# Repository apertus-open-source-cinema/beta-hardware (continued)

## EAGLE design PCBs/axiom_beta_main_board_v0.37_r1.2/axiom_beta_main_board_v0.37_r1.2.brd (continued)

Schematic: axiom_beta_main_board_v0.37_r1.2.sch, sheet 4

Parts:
C1, C1', C3, C3', C5, C5', C7, C7': C0805-A; 0805-A
C2, C2', C4, C4', C6, C6', C8, C8': C0603-A; 0603-A
PAD1, PAD2, PAD3, PAD4, PAD5, PAD6, PAD7, PAD8, PAD9, PAD10, PAD11, PAD12, PAD13, PAD14, PAD15, PAD16: PINPAD1.27MM; 1.2/0.6
PB-NW: DF12(XX)-20DP-0.5V
PB-SE: DF12(XX)-20DP-0.5V
PCIE-NORTH: PCIE-36-AXIOM-NOPEG; PCIE-36-NOPEG
PCIE-SOUTH: PCIE-36-AXIOM-NOPEG; PCIE-36-NOPEG
PWR-NE: PINHD-2X02_2.54; 2X02
PWR-NW: PINHD-2X02_2.54; 2X02
PWR-SE: PINHD-2X02_2.54; 2X02
PWR-SW: PINHD-2X02_2.54; 2X02
R1, R2, R3, R4, R5, R6: 4k7; 0402-B
U1: PCA9540BDP; SOP65P490X300-8N

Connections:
A_!RST: PB-NW.2; also elsewhere on the board
A_SCL: PB-NW.1; also elsewhere on the board
A_SDA: PB-NW.3; also elsewhere on the board
BANK13_00_N: PCIE-NORTH.B17 (LVDS_5B); also elsewhere on the board
BANK13_00_P: PCIE-NORTH.B16 (LVDS_5A); also elsewhere on the board
BANK13_02_N: PCIE-NORTH.A16 (LVDS_4A); also elsewhere on the board
BANK13_02_P: PCIE-NORTH.A17 (LVDS_4B); also elsewhere on the board
BANK13_03_N: PCIE-NORTH.A14 (LVDS_3B); also elsewhere on the board
BANK13_03_P: PCIE-NORTH.A13 (LVDS_3A); also elsewhere on the board
BANK13_04_N: PCIE-SOUTH.A6 (LVDS_1B); also elsewhere on the board
BANK13_04_P: PCIE-SOUTH.A5 (LVDS_1A); also elsewhere on the board
BANK13_05_N: PCIE-SOUTH.A3 (LVDS_0B); also elsewhere on the board
BANK13_05_P: PCIE-SOUTH.A2 (LVDS_0A); also elsewhere on the board
BANK13_06_N: PCIE-SOUTH.A8 (LVDS_2A); also elsewhere on the board
BANK13_06_P: PCIE-SOUTH.A9 (LVDS_2B); also elsewhere on the board
B_!RST: PB-SE.2; also elsewhere on the board
B_SCL: PB-SE.1; also elsewhere on the board
B_SDA: PB-SE.3; also elsewhere on the board
CSO_NE_V: C3.1, C3'.1, C4.1, C4'.1, PAD2.1; also elsewhere on the board
CSO_NW_V: C1.1, C1'.1, C2.1, C2'.1, PAD15.1, PWR-NW.1
CSO_SE_V: C7.1, C7'.1, C8.1, C8'.1, PAD7.1, PWR-SE.1
CSO_SW_V: C5.1, C5'.1, C6.1, C6'.1, PAD10.1; also elsewhere on the board
C_CK_E: PAD5.1; also elsewhere on the board
C_CK_W: PAD13.1; also elsewhere on the board
C_EN_E: PAD3.1; also elsewhere on the board
C_EN_W: PAD11.1; also elsewhere on the board
C_SI_E: PAD4.1; also elsewhere on the board
C_SI_W: PAD12.1; also elsewhere on the board
C_SO_E: PAD6.1; also elsewhere on the board
C_SO_W: PAD14.1; also elsewhere on the board
E_I2C_V: PWR-NE.1; also elsewhere on the board
E_SPI_V: PWR-NE.3; also elsewhere on the board
E_VE_CV: PB-SE.19; also elsewhere on the board
E_VE_OV: PB-SE.10; also elsewhere on the board
E_VE_UV: PB-SE.12; also elsewhere on the board
GND: C1.2, C1'.2, C2.2, C2'.2, C3.2, C3'.2, C4.2, C4'.2, C5.2, C5'.2, C6.2, C6'.2, C7.2, C7'.2, C8.2, C8'.2, PAD1.1, PAD8.1, PAD9.1, PAD16.1, PB-NW.5, PB-SE.5, PCIE-NORTH.A1 (GND), PCIE-NORTH.A4 (GND), PCIE-NORTH.A7 (GND), PCIE-NORTH.A10 (GND), PCIE-NORTH.A12 (GND), PCIE-NORTH.A15 (GND), PCIE-NORTH.A18 (GND), PCIE-NORTH.B15 (GND), PCIE-NORTH.B18 (GND), PCIE-SOUTH.A1 (GND), PCIE-SOUTH.A4 (GND), PCIE-SOUTH.A7 (GND), PCIE-SOUTH.A10 (GND), PCIE-SOUTH.A12 (GND), PCIE-SOUTH.A15 (GND), PCIE-SOUTH.A18 (GND), PCIE-SOUTH.B15 (GND), PCIE-SOUTH.B18 (GND), U1.6 (VSS); also elsewhere on the board
JTAG_V: PWR-SW.3; also elsewhere on the board
JX1_19_N: PCIE-NORTH.A3 (LVDS_0B); also elsewhere on the board
JX1_19_P: PCIE-NORTH.A2 (LVDS_0A); also elsewhere on the board
JX1_21_N: PCIE-NORTH.A6 (LVDS_1B); also elsewhere on the board
JX1_21_P: PCIE-NORTH.A5 (LVDS_1A); also elsewhere on the board
JX1_23_N: PCIE-NORTH.A9 (LVDS_2B); also elsewhere on the board
JX1_23_P: PCIE-NORTH.A8 (LVDS_2A); also elsewhere on the board
JX2_18_N: PCIE-SOUTH.B17 (LVDS_5B); also elsewhere on the board
JX2_18_P: PCIE-SOUTH.B16 (LVDS_5A); also elsewhere on the board
JX2_20_N: PCIE-SOUTH.A17 (LVDS_4B); also elsewhere on the board
JX2_20_P: PCIE-SOUTH.A16 (LVDS_4A); also elsewhere on the board
JX2_22_N: PCIE-SOUTH.A13 (LVDS_3A); also elsewhere on the board
JX2_22_P: PCIE-SOUTH.A14 (LVDS_3B); also elsewhere on the board
N_CHK_V: PB-NW.14; also elsewhere on the board
N_I2C_V: PWR-NE.4; also elsewhere on the board
N_SPI_V: PWR-NE.2; also elsewhere on the board
N_VE_CV: PB-NW.17; also elsewhere on the board
N_VE_OV: PB-NW.8; also elsewhere on the board
N_VE_RS: PB-NW.7; also elsewhere on the board
N_VE_UV: PB-NW.20; also elsewhere on the board
N_VN_CV: PB-NW.15; also elsewhere on the board
N_VN_OV: PB-NW.6; also elsewhere on the board
N_VN_RS: PB-NW.11; also elsewhere on the board
N_VN_UV: PB-NW.18; also elsewhere on the board
N_VW_CV: PB-NW.13; also elsewhere on the board
N_VW_OV: PB-NW.4; also elsewhere on the board
N_VW_RS: PB-NW.9; also elsewhere on the board
N_VW_UV: PB-NW.16; also elsewhere on the board
PCIE_I2C_V: PCIE-NORTH.B3 (V_I2C), PCIE-SOUTH.B3 (V_I2C), R3.1, R4.1, R5.1, R6.1, U1.3 (VDD); also elsewhere on the board
PCIE_N_5V: PCIE-NORTH.B12 (5V); also elsewhere on the board
PCIE_N_IO0: PCIE-NORTH.B4 (IO0); also elsewhere on the board
PCIE_N_IO1: PCIE-NORTH.B5 (IO1); also elsewhere on the board
PCIE_N_IO2: PCIE-NORTH.B6 (IO2); also elsewhere on the board
PCIE_N_IO3: PCIE-NORTH.B7 (IO3); also elsewhere on the board
PCIE_N_IO4: PCIE-NORTH.B8 (IO4); also elsewhere on the board
PCIE_N_IO5: PCIE-NORTH.B9 (IO5); also elsewhere on the board
PCIE_N_IO6: PCIE-NORTH.B10 (IO6); also elsewhere on the board
PCIE_N_IO7: PCIE-NORTH.B11 (IO7); also elsewhere on the board
PCIE_N_SCL: PCIE-NORTH.B2 (SCL), R4.2, U1.5 (SC0)
PCIE_N_SDA: PCIE-NORTH.B1 (SDA), R3.2, U1.4 (SD0)
PCIE_N_V: PCIE-NORTH.B13 (VCC); also elsewhere on the board
PCIE_N_VCCIO: PCIE-NORTH.B14 (VCCIO); also elsewhere on the board
PCIE_SCL: R2.2, U1.1 (SCL); also elsewhere on the board
PCIE_SDA: R1.2, U1.2 (SDA); also elsewhere on the board
PCIE_S_5V: PCIE-SOUTH.B12 (5V); also elsewhere on the board
PCIE_S_IO0: PCIE-SOUTH.B4 (IO0); also elsewhere on the board
PCIE_S_IO1: PCIE-SOUTH.B5 (IO1); also elsewhere on the board
PCIE_S_IO2: PCIE-SOUTH.B6 (IO2); also elsewhere on the board
PCIE_S_IO3: PCIE-SOUTH.B7 (IO3); also elsewhere on the board
PCIE_S_IO4: PCIE-SOUTH.B8 (IO4); also elsewhere on the board
PCIE_S_IO5: PCIE-SOUTH.B9 (IO5); also elsewhere on the board
PCIE_S_IO6: PCIE-SOUTH.B10 (IO6); also elsewhere on the board
PCIE_S_IO7: PCIE-SOUTH.B11 (IO7); also elsewhere on the board
PCIE_S_SCL: PCIE-SOUTH.B2 (SCL), R6.2, U1.8 (SC1)
PCIE_S_SDA: PCIE-SOUTH.B1 (SDA), R5.2, U1.7 (SD1)
PCIE_S_V: PCIE-SOUTH.B13 (VCC); also elsewhere on the board
PCIE_S_VCCIO: PCIE-SOUTH.B14 (VCCIO); also elsewhere on the board
RFAB_E_V: PWR-SE.3; also elsewhere on the board
RFAB_W_V: PWR-NW.3; also elsewhere on the board
SH_NW_V: PWR-NW.4; also elsewhere on the board
SH_NW_VIO: PWR-NW.2, R1.1, R2.1; also elsewhere on the board
SH_SE_V: PWR-SE.4; also elsewhere on the board
SH_SE_VIO: PWR-SE.2; also elsewhere on the board
S_CHK_V: PB-SE.14; also elsewhere on the board
S_I2C_V: PWR-SW.4; also elsewhere on the board
S_SPI_V: PWR-SW.2; also elsewhere on the board
S_VE_CV: PB-SE.13; also elsewhere on the board
S_VE_OV: PB-SE.4; also elsewhere on the board
S_VE_RS: PB-SE.9; also elsewhere on the board
S_VE_UV: PB-SE.16; also elsewhere on the board
S_VS_CV: PB-SE.15; also elsewhere on the board
S_VS_OV: PB-SE.6; also elsewhere on the board
S_VS_RS: PB-SE.11; also elsewhere on the board
S_VS_UV: PB-SE.18; also elsewhere on the board
S_VW_CV: PB-SE.17; also elsewhere on the board
S_VW_OV: PB-SE.8; also elsewhere on the board
S_VW_RS: PB-SE.7; also elsewhere on the board
S_VW_UV: PB-SE.20; also elsewhere on the board
W_I2C_V: PWR-SW.1; also elsewhere on the board
W_VW_CV: PB-NW.19; also elsewhere on the board
W_VW_OV: PB-NW.10; also elsewhere on the board
W_VW_UV: PB-NW.12; also elsewhere on the board

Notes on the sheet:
AXIOM Beta Main Board
Copyright (C) 2015-2020 H.Poetzl Licensed under CERN OHL v.1.2
PCIE, Power, Center Area

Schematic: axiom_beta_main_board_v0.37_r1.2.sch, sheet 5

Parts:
C9, C10, C11, C12, C13, C41: 100n; 0402-B
C19, C20, C21, C22, C23, C24, C25, C26, C27, C28, C29: 10n; 0402-B
HDR-NW: PINHD-2X08_2.00_LPR; 62101621821
HDR-SW: PINHD-2X08_2.00_LPR; 62101621821
R7: 50R; 0402-B
R15: 100R; 0201-B
R18: 10k; 0402-B
RFW: MACHXO2-100; MACHXO2-100TQFP
U2: PIC16F1718-I/MV; QFN40P400X400X55-29N

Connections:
!SS!_W: RFW.27 (CSSPIN), U2.4 (RA5)
!W_RESET!: U2.1 (RA2); also elsewhere on the board
A_!RST: R18.2, U2.26 (RE3/!MCLR!/VPP); also elsewhere on the board
A_SCL: U2.24 (RB6/ICSPCLK); also elsewhere on the board
A_SDA: U2.25 (RB7/ICSPDAT); also elsewhere on the board
BANK13_01_N: R15.2, RFW.38 (PB11A); also elsewhere on the board
BANK13_01_P: R15.1, RFW.39 (PB11B); also elsewhere on the board
BANK13_SE_0: R7.1, RFW.88 (PT12A), U2.7 (RA6); also elsewhere on the board
C_CK_W: RFW.18 (PL8C); also elsewhere on the board
C_EN_W: RFW.14 (PL5C); also elsewhere on the board
C_SI_W: RFW.19 (PL8D); also elsewhere on the board
C_SO_W: RFW.15 (PL5D); also elsewhere on the board
DONE_W: RFW.76 (DONE), U2.20 (RB2)
GND: C9.2, C10.2, C11.2, C12.2, C13.2, C19.2, C20.2, C21.2, C22.2, C23.2, C24.2, C25.2, C26.2, C27.2, C28.2, C29.2, C41.2, HDR-SW.1, HDR-SW.2, R7.2, RFW.6 (GND), RFW.22 (GND), RFW.33 (GND), RFW.44 (GND), RFW.56 (GND), RFW.72 (GND), RFW.79 (GND), RFW.92 (GND), U2.5 (VSS), U2.16 (VSS), U2.29 (EPAD); also elsewhere on the board
INITN_W: RFW.77 (INITN), U2.18 (RB0)
JTAGENB_W: RFW.82 (JTAGENB), U2.14 (RC6)
PB22B_W: RFW.47 (PB18D), U2.23 (RB5)
PCIE_N_IO0: RFW.83 (PT15B); also elsewhere on the board
PCIE_N_IO1: RFW.78 (PT16C); also elsewhere on the board
PCIE_N_IO2: RFW.74 (PR2B); also elsewhere on the board
PCIE_N_IO3: RFW.75 (PR2A); also elsewhere on the board
PCIE_N_IO4: RFW.71 (PR3A); also elsewhere on the board
PCIE_N_IO5: RFW.70 (PR3B); also elsewhere on the board
PCIE_N_IO6: RFW.69 (PR4A); also elsewhere on the board
PCIE_N_IO7: RFW.68 (PR4B); also elsewhere on the board
PCIE_SCL: RFW.86 (SCL), U2.12 (RC4); also elsewhere on the board
PCIE_SDA: RFW.85 (SDA), U2.13 (RC5); also elsewhere on the board
PCIE_S_IO0: RFW.1 (PL2C); also elsewhere on the board
PCIE_S_IO1: RFW.2 (PL2D); also elsewhere on the board
PCIE_S_IO2: RFW.98 (PT9B); also elsewhere on the board
PCIE_S_IO3: RFW.99 (PT9A); also elsewhere on the board
PCIE_S_IO4: RFW.96 (PT10B); also elsewhere on the board
PCIE_S_IO5: RFW.97 (PT10A); also elsewhere on the board
PCIE_S_IO6: RFW.84 (PT15A); also elsewhere on the board
PCIE_S_IO7: RFW.87 (PT12B); also elsewhere on the board
PROGRAMN_W: RFW.81 (PROGRAMN), U2.15 (RC7)
RFAB_W_V: C9.1, C10.1, C19.1, C20.1, RFW.50 (VCC), RFW.100 (VCC); also elsewhere on the board
SCK_W: RFW.31 (MCLK), U2.3 (RA4)
SDI_W: RFW.49 (SI/SISPI), U2.21 (RB3)
SDO_W: RFW.32 (SO/SPISO), U2.2 (RA3)
SH_NW_IO0: HDR-NW.4, RFW.67 (PR4C)
SH_NW_IO1: HDR-NW.3, RFW.66 (PR4D)
SH_NW_IO2: HDR-NW.6, RFW.65 (PR5A)
SH_NW_IO3: HDR-NW.5, RFW.64 (PR5B)
SH_NW_IO4: HDR-NW.8, RFW.63 (PR5C)
SH_NW_IO5: HDR-NW.7, RFW.62 (PR5D)
SH_NW_IO6: HDR-NW.10, RFW.60 (PR8C)
SH_NW_IO7: HDR-NW.9, RFW.59 (PR8D)
SH_NW_IO8: HDR-NW.12, RFW.58 (PR9A)
SH_NW_IO9: HDR-NW.11, RFW.57 (PR9B)
SH_NW_V: HDR-NW.2; also elsewhere on the board
SH_NW_VIO: C11.1, C12.1, C13.1, C21.1, C22.1, C23.1, C24.1, C25.1, C26.1, C27.1, C28.1, C29.1, C41.1, HDR-NW.1, R18.1, RFW.5 (VCCIO5), RFW.11 (VCCIO4), RFW.23 (VCCIO3), RFW.26 (VCCIO2), RFW.46 (VCCIO2), RFW.55 (VCCIO1), RFW.73 (VCCIO1), RFW.80 (VCCIO0), RFW.93 (VCCIO0), U2.17 (VDD); also elsewhere on the board
SH_SW_IO0: HDR-SW.4, RFW.4 (PL3B)
SH_SW_IO1: HDR-SW.3, RFW.3 (PL3A)
SH_SW_IO2: HDR-SW.6, RFW.8 (PL3D)
SH_SW_IO3: HDR-SW.5, RFW.7 (PL3C)
SH_SW_IO4: HDR-SW.8, RFW.10 (PL4B)
SH_SW_IO5: HDR-SW.7, RFW.9 (PL4A)
SH_SW_IO6: HDR-SW.10, RFW.12 (PL5A)
SH_SW_IO7: HDR-SW.9, RFW.13 (PL5B)
SH_SW_IO8: HDR-SW.12, RFW.16 (PL8A)
SH_SW_IO9: HDR-SW.11, RFW.17 (PL8B)
SN_W: RFW.48 (SN), U2.22 (RB4)
S_I2C_EN: U2.28 (RA1); also elsewhere on the board
S_SCK: RFW.28 (PB4D); also elsewhere on the board
S_SCL: RFW.34 (PB9A); also elsewhere on the board
S_SDA: RFW.35 (PB9B); also elsewhere on the board
S_SDI: RFW.30 (PB6B); also elsewhere on the board
S_SDO: RFW.29 (PB6A); also elsewhere on the board
S_SPI_EN: RFW.45 (PB18C); also elsewhere on the board
TCK: RFW.43 (PB18B); also elsewhere on the board
TCK_W: RFW.91 (TCK), U2.10 (RC2)
TDI: RFW.41 (PB15B); also elsewhere on the board
TDI_W: RFW.94 (TDI), U2.9 (RC1)
TDO: RFW.40 (PB15A); also elsewhere on the board
TDO_W: RFW.95 (TDO), U2.8 (RC0)
TMS: RFW.42 (PB18A); also elsewhere on the board
TMS_W: RFW.90 (TMS), U2.11 (RC3)
W_I2C_EN: U2.27 (RA0); also elsewhere on the board
W_SCL: RFW.36 (PB11C); also elsewhere on the board
W_SDA: RFW.37 (PB11D); also elsewhere on the board
XX1_N: HDR-NW.13, RFW.52 (PR10C)
XX1_P: HDR-NW.15, RFW.51 (PR10D)
XX2_N: HDR-NW.14, RFW.54 (PR9C)
XX2_P: HDR-NW.16, RFW.53 (PR9D)
XX3_N: HDR-SW.16, RFW.25 (PL10D)
XX3_P: HDR-SW.14, RFW.24 (PL10C)
XX4_N: HDR-SW.15, RFW.21 (PL9B)
XX4_P: HDR-SW.13, RFW.20 (PL9A)

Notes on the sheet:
AXIOM Beta Main Board
Copyright (C) 2015-2020 H.Poetzl Licensed under CERN OHL v.1.2
Interface Fabric West

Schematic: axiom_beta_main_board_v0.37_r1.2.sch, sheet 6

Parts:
C14, C15, C16, C17, C18, C42: 100n; 0402-B
C30, C31, C32, C33, C34, C35, C36, C37, C38, C39, C40: 10n; 0402-B
HDR-NE: PINHD-2X08_2.00_LPR; 62101621821
HDR-SE: PINHD-2X08_2.00_LPR; 62101621821
R8: 50R; 0402-B
R16, R17: 100R; 0201-B
R19: 10k; 0402-B
RFE: MACHXO2-100; MACHXO2-100TQFP
U3: PIC16F1718-I/MV; QFN40P400X400X55-29N

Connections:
!E_RESET!: U3.1 (RA2); also elsewhere on the board
!SS!_E: RFE.27 (CSSPIN), U3.4 (RA5)
B_!RST: R19.2, U3.26 (RE3/!MCLR!/VPP); also elsewhere on the board
B_SCL: U3.24 (RB6/ICSPCLK); also elsewhere on the board
B_SDA: U3.25 (RB7/ICSPDAT); also elsewhere on the board
C_CK_E: RFE.18 (PL8C); also elsewhere on the board
C_EN_E: RFE.14 (PL5C); also elsewhere on the board
C_SI_E: RFE.19 (PL8D); also elsewhere on the board
C_SO_E: RFE.15 (PL5D); also elsewhere on the board
DONE_E: RFE.76 (DONE), U3.20 (RB2)
E_EN: RFE.20 (PL9A); also elsewhere on the board
E_I2C_EN: U3.27 (RA0); also elsewhere on the board
E_IO0: RFE.99 (PT9A)
E_IO1: RFE.98 (PT9B)
E_IO2: RFE.97 (PT10A)
E_IO3: RFE.96 (PT10B)
E_IO5: RFE.87 (PT12B)
E_IO6: RFE.84 (PT15A)
E_IO7: RFE.83 (PT15B)
E_SCK: RFE.21 (PL9B); also elsewhere on the board
E_SCL: RFE.36 (PB11C); also elsewhere on the board
E_SDA: RFE.37 (PB11D); also elsewhere on the board
E_SDI: RFE.24 (PL10C); also elsewhere on the board
E_SDO: RFE.25 (PL10D); also elsewhere on the board
GND: C14.2, C15.2, C16.2, C17.2, C18.2, C30.2, C31.2, C32.2, C33.2, C34.2, C35.2, C36.2, C37.2, C38.2, C39.2, C40.2, C42.2, HDR-NE.1, HDR-NE.2, R8.2, RFE.6 (GND), RFE.22 (GND), RFE.33 (GND), RFE.44 (GND), RFE.56 (GND), RFE.72 (GND), RFE.79 (GND), RFE.92 (GND), U3.5 (VSS), U3.16 (VSS), U3.29 (EPAD); also elsewhere on the board
INITN_E: RFE.77 (INITN), U3.18 (RB0)
IO_SCL: RFE.86 (SCL), U3.12 (RC4)
IO_SDA: RFE.85 (SDA), U3.13 (RC5)
JTAGENB_E: RFE.82 (JTAGENB), U3.14 (RC6)
JX1_01_N: HDR-NE.13; also elsewhere on the board
JX1_01_P: HDR-NE.15; also elsewhere on the board
JX1_03_N: HDR-NE.14; also elsewhere on the board
JX1_03_P: HDR-NE.16; also elsewhere on the board
JX1_05_N: R16.2, RFE.35 (PB9B); also elsewhere on the board
JX1_05_P: R16.1, RFE.34 (PB9A); also elsewhere on the board
JX1_SE_0: R8.1, RFE.88 (PT12A), U3.7 (RA6); also elsewhere on the board
JX2_00_N: HDR-SE.14; also elsewhere on the board
JX2_00_P: HDR-SE.16; also elsewhere on the board
JX2_02_N: HDR-SE.13; also elsewhere on the board
JX2_02_P: HDR-SE.15; also elsewhere on the board
JX2_04_N: R17.1, RFE.38 (PB11A); also elsewhere on the board
JX2_04_P: R17.2, RFE.39 (PB11B); also elsewhere on the board
N_I2C_EN: U3.28 (RA1); also elsewhere on the board
N_IO0: RFE.1 (PL2C); also elsewhere on the board
N_IO1: RFE.2 (PL2D)
N_SCK: RFE.42 (PB18A); also elsewhere on the board
N_SCL: RFE.28 (PB4D); also elsewhere on the board
N_SDA: RFE.30 (PB6B); also elsewhere on the board
N_SDI: RFE.29 (PB6A); also elsewhere on the board
N_SDO: RFE.43 (PB18B); also elsewhere on the board
N_SPI_EN: RFE.45 (PB18C); also elsewhere on the board
PB22B_E: RFE.47 (PB18D), U3.23 (RB5)
PROGRAMN_E: RFE.81 (PROGRAMN), U3.15 (RC7)
RFAB_E_V: C14.1, C15.1, C30.1, C31.1, RFE.50 (VCC), RFE.100 (VCC); also elsewhere on the board
SCK_E: RFE.31 (MCLK), U3.3 (RA4)
SDI_E: RFE.49 (SI/SISPI), U3.21 (RB3)
SDO_E: RFE.32 (SO/SPISO), U3.2 (RA3)
SH_NE_IO0: HDR-NE.4, RFE.4 (PL3B)
SH_NE_IO1: HDR-NE.3, RFE.3 (PL3A)
SH_NE_IO2: HDR-NE.6, RFE.8 (PL3D)
SH_NE_IO3: HDR-NE.5, RFE.7 (PL3C)
SH_NE_IO4: HDR-NE.8, RFE.10 (PL4B)
SH_NE_IO5: HDR-NE.7, RFE.9 (PL4A)
SH_NE_IO6: HDR-NE.10, RFE.12 (PL5A)
SH_NE_IO7: HDR-NE.9, RFE.13 (PL5B)
SH_NE_IO8: HDR-NE.12, RFE.16 (PL8A)
SH_NE_IO9: HDR-NE.11, RFE.17 (PL8B)
SH_SE_IO0: HDR-SE.4, RFE.67 (PR4C)
SH_SE_IO1: HDR-SE.3, RFE.66 (PR4D)
SH_SE_IO2: HDR-SE.6, RFE.65 (PR5A)
SH_SE_IO3: HDR-SE.5, RFE.64 (PR5B)
SH_SE_IO4: HDR-SE.8, RFE.63 (PR5C)
SH_SE_IO5: HDR-SE.7, RFE.62 (PR5D)
SH_SE_IO6: HDR-SE.10, RFE.60 (PR8C)
SH_SE_IO7: HDR-SE.9, RFE.59 (PR8D)
SH_SE_IO8: HDR-SE.12, RFE.58 (PR9A)
SH_SE_IO9: HDR-SE.11, RFE.57 (PR9B)
SH_SE_V: HDR-SE.2; also elsewhere on the board
SH_SE_VIO: C16.1, C17.1, C18.1, C32.1, C33.1, C34.1, C35.1, C36.1, C37.1, C38.1, C39.1, C40.1, C42.1, HDR-SE.1, R19.1, RFE.5 (VCCIO5), RFE.11 (VCCIO4), RFE.23 (VCCIO3), RFE.26 (VCCIO2), RFE.46 (VCCIO2), RFE.55 (VCCIO1), RFE.73 (VCCIO1), RFE.80 (VCCIO0), RFE.93 (VCCIO0), U3.17 (VDD); also elsewhere on the board
SN_E: RFE.48 (SN), U3.22 (RB4)
S_IO0: RFE.75 (PR2A); also elsewhere on the board
S_IO1: RFE.74 (PR2B)
S_IO2: RFE.71 (PR3A)
S_IO3: RFE.70 (PR3B)
S_IO4: RFE.69 (PR4A)
S_IO5: RFE.68 (PR4B)
S_IO6: RFE.54 (PR9C)
S_IO7: RFE.53 (PR9D)
S_IO8: RFE.52 (PR10C)
S_IO9: RFE.51 (PR10D)
TCK_E: RFE.91 (TCK), U3.10 (RC2)
TDI_E: RFE.94 (TDI), U3.9 (RC1)
TDO_E: RFE.95 (TDO), U3.8 (RC0)
TMS_E: RFE.90 (TMS), U3.11 (RC3)

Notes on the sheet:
AXIOM Beta Main Board
Copyright (C) 2015-2020 H.Poetzl Licensed under CERN OHL v.1.2
Interface Fabric East

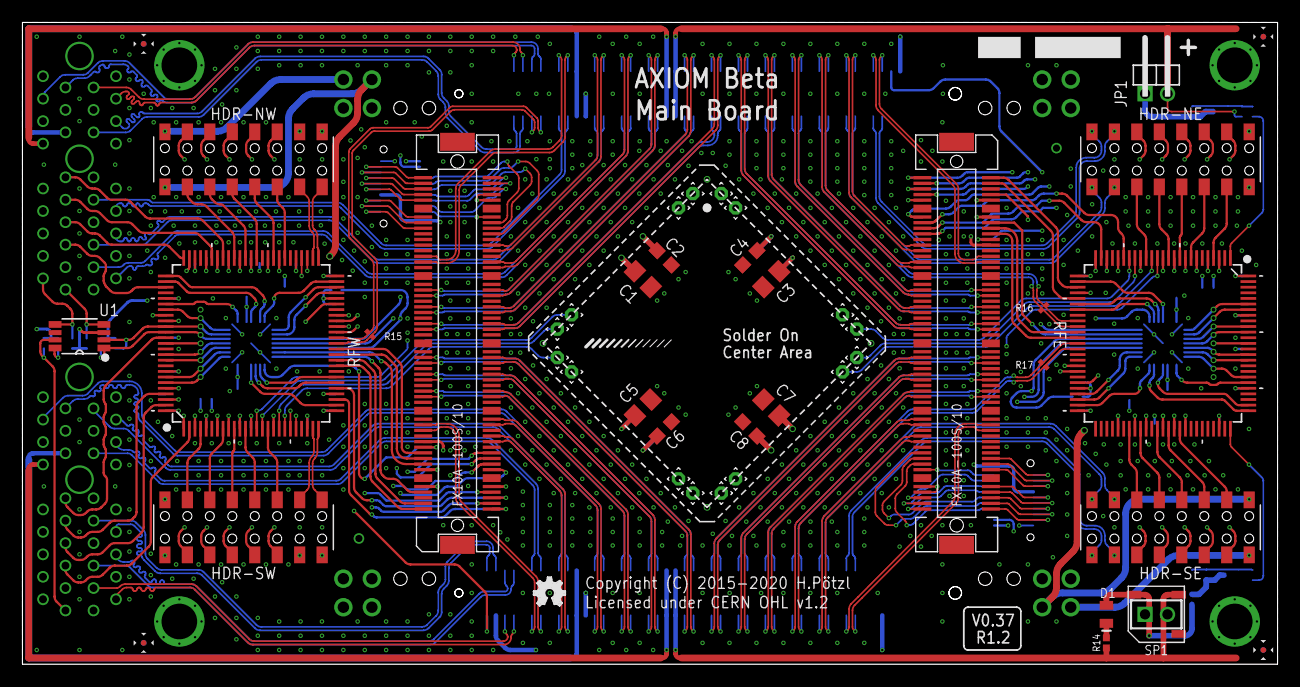
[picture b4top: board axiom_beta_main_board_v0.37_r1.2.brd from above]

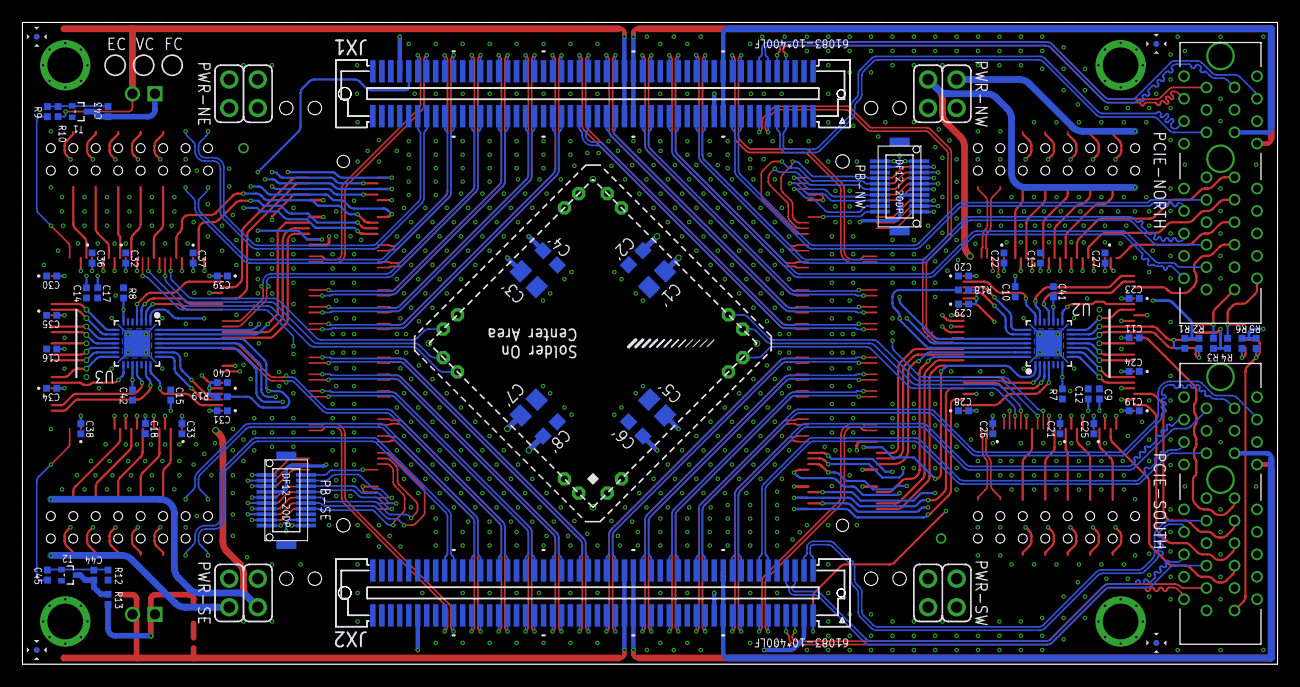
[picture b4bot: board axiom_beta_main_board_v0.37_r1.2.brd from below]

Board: 4 copper layers, 111.8 x 57.1 mm, 124 parts (78 on the bottom side), 324 nets.

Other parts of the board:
LOGO1: OSHW_LOGO_FILLX0100-NT; OSHW_FILLX100_NOTEXT

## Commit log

2014-05-17 new version with redesigned enclosure based on Janoschs ideas
2014-06-19 more progress
2014-07-15 more enclosure progress
2014-07-15 progress
2014-07-15 progess
2014-07-16 even more progress
2014-07-16 added UnMate 01
2014-07-18 updated pcb module CAD and drawings
2014-07-19 several fixes
2014-07-22 added hexsaver
2014-08-26 added screw models
2014-10-21 added image sensor model
2014-10-21 color update
2014-10-29 added cmosis image sensor datasheets
2014-10-31 added new backplate variant and top plate riser
2014-11-11 stack concept V2
2014-12-10 new concept with high speed IO on pcie x4 connector
2014-12-14 pcie x1 part added
2014-12-14 latest files
2015-01-05 added updated cmosis datasheets
2015-01-08 added version one of the prototype skeleton 3d print part
2015-02-10 IO shield enclosure concepts
2015-02-17 new top and bend front parts
2015-02-17 updated assembly
2015-02-22 added f-mount component from AXIOM Alpha
2015-02-22 updated PCB thickness and added power board PCB
2015-02-22 replaced PCIe component with the one actually being used
2015-02-22 zynq and pcie imported components added
2015-02-22 remove obsolete files
2015-02-22 gitignore updated
2015-02-22 removed outdated pcie connector
2015-02-22 renamed
2015-02-22 removed some outdated files, added DP connector
2015-02-22 DP connector import
2015-02-23 updated modules and assembly
2015-03-03 added latest datasheets
2015-03-13 Beta Skeleton
    Added Beta Skeleton V02 files
2015-03-13 Beta Skeleton moved
    Skeleton files moved in skeleton folder
2015-03-13 added nikon mount 3d print part
2015-03-22 skeleton version 2 finished
2015-03-24 sensor cooler preliminary model added
2015-04-02 new skeleton variation
2015-04-02 update skeleton v3
2015-04-02 update to fix small gap in assembly
2015-04-02 additional exports
2015-04-02 stack export
2015-04-03 fixed geometry by combining all parts into one
2015-04-03 added new variant
2015-04-03 Revert "added new variant"
    This reverts commit 700cb322e26e7451e2671acac1bbda0ab89976b3.
2015-04-03 microzed cut ipt
2015-04-03 new variant
2015-04-04 added rotated version
2015-04-04 add Skeleton_E-mount files
    used to mount a 10mm E-Mount tube in front of the CMV12000 image sensor
2015-04-04 added Sensormount with higher base
    Base is raised to 50mm from the axis to fit the Nikon and Canon
    lensadapers.
2015-04-28 Added H shaped adapter CMV12000 to E-mount
    Added H shaped adapter CMV12000 to E-mount
2015-04-28 added H shaped adapter CMV12000 to E-mount .stl
    added H shaped adapter CMV12000 to E-mount .stl
2015-06-02 added step file of PCB assembly
2015-07-12 updated dimenions
2015-07-12 Simple Design Update
2015-07-13 updated step file
2015-08-27 updated new version of stack design
2015-08-27 added dwg
2015-09-08 added emount
2015-09-24 added new simple design for 3d printing
2015-09-24 simpledesign v2
2015-10-08 added final skeleton step files
2015-10-08 added latest emount skeleton STL
2015-10-13 latest datasheets updated
2015-10-15 module holder
2015-10-15 fixed dimensions
2015-10-15 updated hole diameters
2015-10-15 added hdmi pluging module
2015-10-15 increased size of cooling fan
2015-10-15 bigger fan
2015-10-15 simple back
2015-10-15 added
2015-10-30 new version
2015-10-30 made the part stronger and thicker
2015-10-30 smoother surfaces and distance fix
2015-10-31 added complete assembly stl
2015-10-31 added skeleton and pcb assembly as step file
2016-01-03 added simple design 3d print
2016-01-03 moved 3d print parts to own subfolder
2016-01-03 removed folder
2016-02-12 added new 3d print parts
2016-02-12 updated 3d print parts
2016-02-12 moved outdated version to archived folder
2016-02-12 file uploaded
2016-02-12 added Skeleton Emount part for 3d print assembly
2016-03-16 added latest CMV12000 V2 datasheet
2016-04-12 added pcb separator tool
2016-05-18 dimensions corrected, design simplified
2016-05-18 fixed dimensions and simplified design
2016-06-19 improved 3d printability
2016-07-31 updated with real world measurements
2016-08-01 added e mount cap
2016-08-06 updated simple enclosure with V02
2016-08-06 added reflow bracket tool
2016-08-06 fixed centimeter -> millimeter export mistake
2016-08-10 reduced 1mm overlap to 0.5mm
2016-08-11 added hotplate files
2016-08-13 updated e mount cap
2016-09-15 step added
2016-09-16 added cmv12000 extraction tool
2016-09-16 added rubberband grooves
2016-09-18 updated and ready for first 3d print test
2016-09-18 fixed problem
2016-10-17 added heatsink model
2016-10-21 updated simple enclosure
2016-10-21 step file upload
2016-11-09 improve README.md
2017-08-17 added license
2018-02-21 add main PCBs
2018-02-21 add Plugin Modules and Shields
2018-02-21 update README
    - changed image to the PCB stack, so the boards in this repo are visible
    - fixed notation errors
2018-03-07 typo fix
2020-07-19 updated image sensor datasheets
2020-12-09 added recent PCBs
2020-12-09 Backlink to CADLAB.io has been added.
